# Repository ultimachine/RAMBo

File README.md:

RAMBo 3D Printer electronics
=====

THIS board is based off the Arduino MEGA design and work of RepRap community. It has 5 stepper drivers and 5 mosfet switched outputs.

There is no warantee for these files in any way. They are used to produce these boards, but there may have been some undocumented tweaks by various designers, engineers, manufacturers, suppliers, and assemblers to make this a functional product.

If you have any questions, suggestions, or comments please use the issues tracker at github.org/ultimachine/RAMBo/issues for now.

Please report bugs at github.org/ultimachine/RAMBo/issues

Documentation is at reprap.org/wiki/rambo

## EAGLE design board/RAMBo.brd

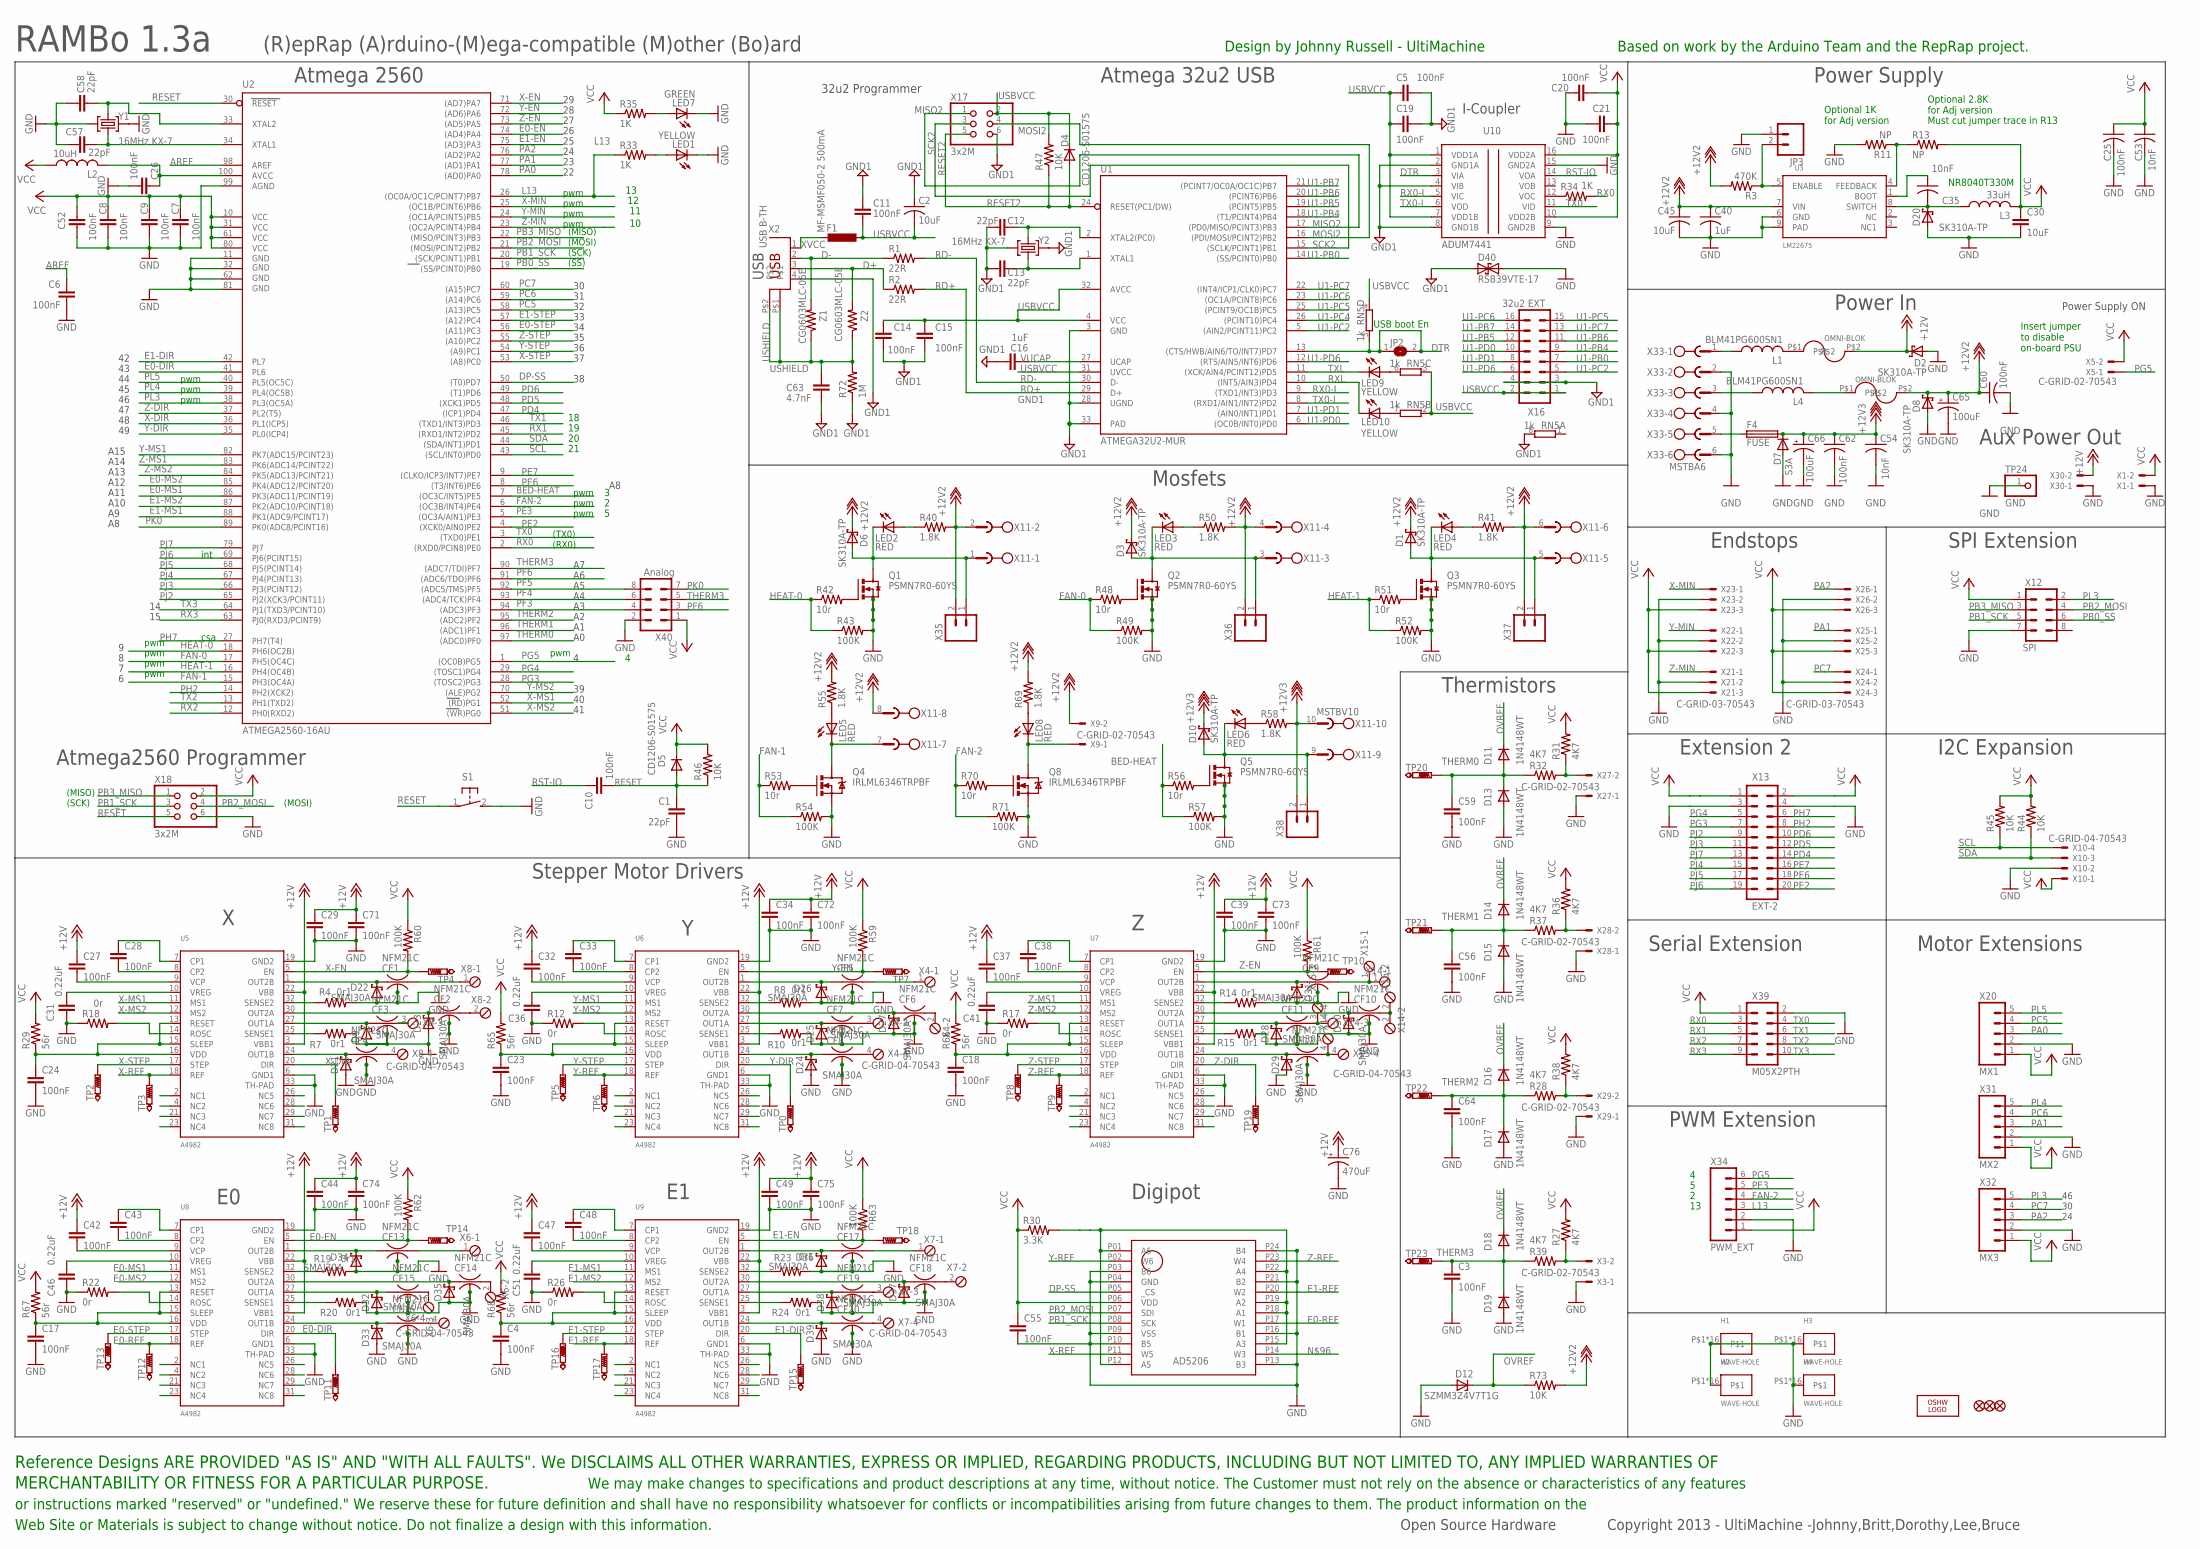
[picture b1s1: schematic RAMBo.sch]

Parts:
C1, C12, C13, C57, C58: 22pF; C0603
C2: 10uF; C0805
C3, C4, C6, C7, C8, C9, C10, C11, C14, C15, C17, C18, C23, C24, C25, C26, C27, C28, C29, C32, C33, C34, C37, C38, C39, C42, C43, C44, C47, C48, C49, C52, C55, C56, C59, C60, C62, C64, C71, C72, C73, C74, C75: 100nF; C0603
C5, C19, C20, C21: 100nF; C0402
C16: 1uF; C0603
C30: 10uF; C1210K
C31, C36, C41, C46, C51: 0.22uF; C0603
C35, C53, C54: 10nF; C0603
C40: 1uF; C0805
C45: 10uF; C2220K
C63: 4.7nF; C0402
C65, C66: 100uF; E3,5-8
C76: 470uF; C12,5-5
CF1, CF2, CF3, CF4, CF5, CF6, CF7, CF8, CF9, CF10, CF11, CF12, CF13, CF14, CF15, CF16, CF17, CF18, CF19, CF20: NFM21C
D1, D2, D3, D6, D8, D10, D20: SK310A-TP; SMA-SM
D4, D5: CD1206-S01575; MINIMELF
D7: S3A; DO-214AB
D9, D21, D22, D23, D24, D25, D26, D27, D28, D29, D30, D31, D32, D33, D34, D35, D36, D37, D38, D39: SMAJ30A; SMA-SM
D11, D13, D14, D15, D16, D17, D18, D19: 1N4148WT; SOD523
D12: SZMM3Z4V7T1G; SOD323-R
D40: RSB39VTE-17; SOD323-R
F1: MF-MSMF050-2 500mA; L1812
F2, F3: OMNI-BLOK
F4: FUSE; FUSE-ATO-SMD
FID1, FID2, FID3: FIDUCIAL1X2.5; FIDUCIAL-1X2.5
H1, H2, H3, H4: WAVE-HOLE; 3,0-WAVE-HOLE
JP2: SJ
JP3: M02PTH; 1X02
L1, L4: BLM41PG600SN1; L1806
L2: 10uH; C0805
L3: 33uH; NR8040
LED1, LED9, LED10: YELLOW; CHIP-LED0805
LED2, LED3, LED4, LED5, LED6, LED8: RED; CHIP-LED0805
LED7: GREEN; CHIP-LED0805
LOGO1: OSHW_LOGO_8MILX0150-NT; OSHW_8X150_NOTEXT
Q1, Q2, Q3, Q5: PSMN7R0-60YS; SOT669
Q4, Q8: IRLML6346TRPBF; SOT23-3
R1, R2: 22R; R0402
R3: 470K; R0603
R4, R7, R8, R10, R14, R15, R19, R20, R23, R24: 0r1; R1206
R11, R13: NP; R0603
R12, R17, R18, R22, R26: 0r; R0603
R27, R28, R31, R32, R36, R37, R38, R39: 4K7; R0603
R29, R65, R66, R67, R68: 56r; R0603
R30: 3.3K; R0603
R33, R34, R35: 1K; R0603
R40, R41, R50, R55, R58, R69: 1.8K; R0603
R42, R48, R51, R53, R56, R70: 10r; R0603
R43, R49, R52, R54, R57, R59, R60, R61, R62, R63, R71: 100K; R0603
R44, R45, R46, R47, R73: 10K; R0603
R72: 1M; R0402
RN5: 1k; CAY16
S1: 31-XX; B3F-31XX
TP0, TP1, TP2, TP3, TP4, TP5, TP6, TP7, TP8, TP9, TP10, TP11, TP12, TP13, TP14, TP15, TP16, TP17, TP18, TP19: PTR1B1,27TH; B1,27TH
TP20, TP21, TP22, TP23: PTR1B1,27; B1,27
TP24: GND; 1X01
U1: ATMEGA32U2-MUR; QFN32TROUND
U2: ATMEGA2560-16AU; TQFP100
U3: LM22675; SOIC127P600X170-9N
U4: AD5206; TSSOP24
U5, U6, U7, U8, U9: A4982; QFN32TROUND
U10: ADUM7441; QSOP16
X1, X3, X5, X9, X27, X28, X29, X30: C-GRID-02-70543; 70543-02
X2: USB B-TH; PN61729
X4, X6, X7, X8, X14, X15: C-GRID-04-70543; 4POL254
X10: C-GRID-04-70543; 70543-04
X11: MSTBV10
X12: SPI; 2X4
X13: EXT-2; 2X10
X16: 32u2 EXT; 2X8
X17, X18: 3x2M; 2X03
X20: MX1; 1X05
X21, X22, X23, X24, X25, X26: C-GRID-03-70543; 70543-03
X31: MX2; 1X05
X32: MX3; 1X05
X33: MSTBA6
X34: PWM_EXT; 1X06
X35, X36, X37, X38: M02PTH; 1X02
X39: M05X2PTH; AVR_ICSP
X40: Analog; 2X4
Y1, Y2: 16MHz KX-7; CRYSTAL-3.2-2.5
Z1, Z2: CG0603MLC-05E; R0603

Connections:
+12V: C27.1, C29.1, C32.1, C34.1, C37.1, C39.1, C42.1, C44.1, C47.1, C49.1, C71.1, C72.1, C73.1, C74.1, C75.1, C76.+, D2.C, F2.P$2, U5.3 (VBB1), U5.22 (VBB), U6.3 (VBB1), U6.22 (VBB), U7.3 (VBB1), U7.22 (VBB), U8.3 (VBB1), U8.22 (VBB), U9.3 (VBB1), U9.22 (VBB), X30.2
+12V2: C40.1, C45.1, C60.1, C65.+, D1.C, D3.C, D6.C, D8.C, F3.P$2, R3.2, R40.2, R41.2, R50.2, R55.2, R69.2, R73.2, U3.7 (VIN), X9.2, X11.2, X11.4, X11.6, X11.8, X35.2, X36.2, X37.2
+12V3: C54.1, C62.1, C66.+, D7.C, D10.C, F4.P$2 (2), R58.2, X11.10, X38.2
AREF: C6.1, U2.98 (AREF)
BED-HEAT: R56.1, R57.1, U2.7 ((OC3C/INT5)PE5)
D+: R2.1, X2.3, Z2.2
D-: R1.1, X2.2, Z1.2
DP-SS: U2.50 ((T0)PD7), U4.P05 (_CS)
DTR: JP2.1, JP2.2, RN5.5 (2), U1.13 ((CTS/HWB/AIN6/TO/INT7)PD7), U10.3 (VIA)
E0-DIR: TP11.TP, U2.41 (PL6), U8.20 (DIR)
E0-EN: R62.2, TP14.TP, U2.74 ((AD4)PA4), U8.5 (EN)
E0-MS1: U2.86 (PK3(ADC11/PCINT19)), U8.11 (MS1)
E0-MS2: U2.85 (PK4(ADC12/PCINT20)), U8.12 (MS2)
E0-REF: TP12.TP, U4.P17 (W1), U8.18 (REF)
E0-STEP: TP13.TP, U2.56 ((A11)PC3), U8.17 (STEP)
E1-DIR: TP15.TP, U2.42 (PL7), U9.20 (DIR)
E1-EN: R63.2, TP18.TP, U2.75 ((AD3)PA3), U9.5 (EN)
E1-MS1: U2.88 (PK1(ADC9/PCINT17)), U9.11 (MS1)
E1-MS2: U2.87 (PK2(ADC10/PCINT18)), U9.12 (MS2)
E1-REF: TP17.TP, U4.P20 (W2), U9.18 (REF)
E1-STEP: TP16.TP, U2.57 ((A12)PC4), U9.17 (STEP)
FAN-0: R48.1, R49.1, U2.17 (PH5(OC4C))
FAN-1: R53.1, R54.1, U2.15 (PH3(OC4A))
FAN-2: R70.1, R71.1, U2.6 ((OC3B/INT4)PE4), X34.4
GND: C1.2, C3.2, C4.2, C6.2, C7.2, C8.2, C9.2, C17.2, C18.2, C20.2, C21.1, C23.2, C24.2, C25.2, C26.2, C29.2, C30.2, C31.1, C34.2, C36.1, C39.2, C40.2, C41.1, C44.2, C45.2, C46.1, C49.2, C51.1, C52.2, C53.2, C54.2, C55.2, C56.2, C57.2, C58.2, C59.2, C60.2, C62.2, C64.2, C65.-, C66.-, C71.2, C72.2, C73.2, C74.2, C75.2, C76.-, CF1.2@1 (2), CF1.2@2 (2), CF2.2@1 (2), CF2.2@2 (2), CF3.2@1 (2), CF3.2@2 (2), CF4.2@1 (2), CF4.2@2 (2), CF5.2@1 (2), CF5.2@2 (2), CF6.2@1 (2), CF6.2@2 (2), CF7.2@1 (2), CF7.2@2 (2), CF8.2@1 (2), CF8.2@2 (2), CF9.2@1 (2), CF9.2@2 (2), CF10.2@1 (2), CF10.2@2 (2), CF11.2@1 (2), CF11.2@2 (2), CF12.2@1 (2), CF12.2@2 (2), CF13.2@1 (2), CF13.2@2 (2), CF14.2@1 (2), CF14.2@2 (2), CF15.2@1 (2), CF15.2@2 (2), CF16.2@1 (2), CF16.2@2 (2), CF17.2@1 (2), CF17.2@2 (2), CF18.2@1 (2), CF18.2@2 (2), CF19.2@1 (2), CF19.2@2 (2), CF20.2@1 (2), CF20.2@2 (2), D2.A, D7.A, D8.A, D9.A, D12.A, D13.A, D15.A, D17.A, D19.A, D20.A, D21.A, D22.A, D23.A, D24.A, D25.A, D26.A, D27.A, D28.A, D29.A, D30.A, D31.A, D32.A, D33.A, D34.A, D35.A, D36.A, D37.A, D38.A, D39.A, D40.C (2), H1.P$1, H1.P$2, H1.P$3, H1.P$4, H1.P$5, H1.P$6, H1.P$7, H1.P$8, H1.P$17, H1.P$18, H1.P$19, H1.P$20, H1.P$21, H1.P$22, H1.P$23, H1.P$24, H2.P$1, H2.P$2, H2.P$3, H2.P$4, H2.P$5, H2.P$6, H2.P$7, H2.P$8, H2.P$17, H2.P$18, H2.P$19, H2.P$20, H2.P$21, H2.P$22, H2.P$23, H2.P$24, H3.P$1, H3.P$2, H3.P$3, H3.P$4, H3.P$5, H3.P$6, H3.P$7, H3.P$8, H3.P$17, H3.P$18, H3.P$19, H3.P$20, H3.P$21, H3.P$22, H3.P$23, H3.P$24, H4.P$1, H4.P$2, H4.P$3, H4.P$4, H4.P$5, H4.P$6, H4.P$7, H4.P$8, H4.P$17, H4.P$18, H4.P$19, H4.P$20, H4.P$21, H4.P$22, H4.P$23, H4.P$24, JP3.1, LED1.C, LED7.C, Q1.1 (S), Q1.2 (S), Q1.3 (S), Q2.1 (S), Q2.2 (S), Q2.3 (S), Q3.1 (S), Q3.2 (S), Q3.3 (S), Q4.2 (S), Q5.1 (S), Q5.2 (S), Q5.3 (S), Q8.2 (S), R4.2, R7.2, R8.2, R10.2, R11.2, R12.1, R14.2, R15.2, R17.1, R18.1, R19.2, R20.2, R22.1, R23.2, R24.2, R26.1, R43.2, R49.2, R52.2, R54.2, R57.2, R71.2, S1.2 (S), TP24.1, U2.11 (GND), U2.32 (GND1), U2.62 (GND2), U2.81 (GND3), U2.99 (AGND), U3.6 (GND), U3.9 (PAD), U4.P03 (B6), U4.P04 (GND), U4.P09 (VSS), U4.P10 (B5), U4.P13 (B3), U4.P16 (B1), U4.P21 (B2), U4.P24 (B4), U5.6 (GND1), U5.19 (GND2), U5.33 (TH-PAD), U6.6 (GND1), U6.19 (GND2), U6.33 (TH-PAD), U7.6 (GND1), U7.19 (GND2), U7.33 (TH-PAD), U8.6 (GND1), U8.19 (GND2), U8.33 (TH-PAD), U9.6 (GND1), U9.19 (GND2), U9.33 (TH-PAD), U10.9 (GND2B), U10.15 (GND2A), X1.1, X3.1, X10.2, X12.7, X13.3, X13.4, X18.6, X20.2, X21.2, X22.2, X23.2, X24.2, X25.2, X26.2, X27.1, X28.1, X29.1, X30.1, X31.2, X32.2, X33.2, X33.4, X33.6, X34.2, X39.2, X40.2, Y1.2 (GND), Y1.4 (GND)
GND1: C2.1, C5.2, C11.2, C12.2, C13.2, C14.2, C15.2, C16.2, C19.2, C63.2, D40.A (1), R72.1, RN5.8 (2), U1.3 (GND), U1.28 (UGND), U1.33 (PAD), U10.2 (GND1A), U10.4 (VIB), U10.8 (GND1B), X2.4, X16.3, X16.4, X17.6, Y2.2 (GND), Y2.4 (GND)
HEAT-0: R42.1, R43.1, U2.18 (PH6(OC2B))
HEAT-1: R51.1, R52.1, U2.16 (PH4(OC4B))
L13: R33.1, U2.26 ((OC0A/OC1C/PCINT7)PB7), X34.3
MISO2: U1.17 ((PD0/MISO/PCINT3)PB3), X17.1
MOSI2: U1.16 ((PDI/MOSI/PCINT2)PB2), X17.4
unnamed: C31.2, U5.10 (VREG)
unnamed: LED1.A, R33.2
unnamed: LED7.A, R35.2
unnamed: R8.1, U6.32 (SENSE2)
unnamed: R10.1, U6.25 (SENSE1)
unnamed: C33.2, U6.8 (CP2)
unnamed: C32.2, U6.9 (VCP)
unnamed: C36.2, U6.10 (VREG)
unnamed: R12.2, U6.14 (ROSC)
unnamed: Q4.1 (G), R53.2
unnamed: LED10.A, RN5.7 (2)
unnamed: C24.1, R29.1, U5.13 (RESET), U5.15 (SLEEP), U5.16 (VDD)
unnamed: L1.P$1 (1), X33.1
unnamed: F3.P$1, L4.P$2 (2)
unnamed: JP3.2, R3.1, U3.5 (ENABLE)
unnamed: F4.P$1 (1), X33.5
unnamed: CF5.1, D26.C, U6.1 (OUT2B)
unnamed: CF20.3, X7.4
unnamed: CF5.3, X4.1
unnamed: CF6.1, D27.C, U6.30 (OUT2A)
unnamed: D6.A, LED2.C, Q1.MB (D), X11.1, X35.1
unnamed: R4.1, U5.32 (SENSE2)
unnamed: CF7.1, D25.C, U6.27 (OUT1A)
unnamed: C33.1, U6.7 (CP1)
unnamed: C23.1, R65.1, U6.13 (RESET), U6.15 (SLEEP), U6.16 (VDD)
unnamed: Q2.4 (G), R48.2
unnamed: C26.1, L2.2, U2.100 (AVCC)
unnamed: R14.1, U7.32 (SENSE2)
unnamed: R15.1, U7.25 (SENSE1)
unnamed: C38.2, U7.8 (CP2)
unnamed: C37.2, U7.9 (VCP)
unnamed: C41.2, U7.10 (VREG)
unnamed: R17.2, U7.14 (ROSC)
unnamed: CF10.1, D30.C, U7.30 (OUT2A)
unnamed: CF11.1, D28.C, U7.27 (OUT1A)
unnamed: R7.1, U5.25 (SENSE1)
unnamed: C28.2, U5.8 (CP2)
unnamed: C27.2, U5.9 (VCP)
unnamed: CF19.3, X7.3
unnamed: CF12.1, D29.C, U7.24 (OUT1B)
unnamed: CF12.3, X14.4, X15.4
unnamed: C38.1, U7.7 (CP1)
unnamed: R18.2, U5.14 (ROSC)
unnamed: C18.1, R66.1, U7.13 (RESET), U7.15 (SLEEP), U7.16 (VDD)
unnamed: LED8.C, Q8.3 (D), X9.1
unnamed: R19.1, U8.32 (SENSE2)
unnamed: CF1.1, D22.C, U5.1 (OUT2B)
unnamed: C28.1, U5.7 (CP1)
unnamed: R20.1, U8.25 (SENSE1)
unnamed: C43.2, U8.8 (CP2)
unnamed: CF3.1, D9.C, U5.27 (OUT1A)
unnamed: CF4.1, D21.C, U5.24 (OUT1B)
unnamed: LED9.A, RN5.6 (2)
unnamed: R34.1, U10.12 (VOC)
unnamed: C42.2, U8.9 (VCP)
unnamed: C46.2, U8.10 (VREG)
unnamed: R22.2, U8.14 (ROSC)
unnamed: CF13.1, D34.C, U8.1 (OUT2B)
unnamed: CF13.3, X6.1
unnamed: CF14.1, D35.C, U8.30 (OUT2A)
unnamed: CF15.1, D32.C, U8.27 (OUT1A)
unnamed: C43.1, U8.7 (CP1)
unnamed: C17.1, R67.1, U8.13 (RESET), U8.15 (SLEEP), U8.16 (VDD)
unnamed: CF18.3, X7.2
unnamed: R23.1, U9.32 (SENSE2)
unnamed: R24.1, U9.25 (SENSE1)
unnamed: C48.2, U9.8 (CP2)
unnamed: C47.2, U9.9 (VCP)
unnamed: C51.2, U9.10 (VREG)
unnamed: R26.2, U9.14 (ROSC)
unnamed: CF20.1, D39.C, U9.24 (OUT1B)
unnamed: CF19.1, D38.C, U9.27 (OUT1A)
unnamed: CF17.1, D36.C, U9.1 (OUT2B)
unnamed: CF18.1, D37.C, U9.30 (OUT2A)
unnamed: C48.1, U9.7 (CP1)
unnamed: C4.1, R68.1, U9.13 (RESET), U9.15 (SLEEP), U9.16 (VDD)
unnamed: LED8.A, R69.1
unnamed: Q8.1 (G), R70.2
unnamed: LED2.A, R40.1
unnamed: R30.2, U4.P01 (A6), U4.P12 (A5), U4.P15 (A3), U4.P18 (A1), U4.P19 (A2), U4.P22 (A4)
unnamed: R31.1, R32.2, X27.2
unnamed: Q1.4 (G), R42.2
unnamed: R36.1, R37.2, X28.2
unnamed: Q3.4 (G), R51.2
unnamed: R28.2, R38.1, X29.2
unnamed: Q5.4 (G), R56.2
unnamed: CF17.3, X7.1
unnamed: CF16.3, X6.4
unnamed: CF15.3, X6.3
unnamed: D3.A, LED3.C, Q2.MB (D), X11.3, X36.1
unnamed: LED3.A, R50.1
unnamed: D1.A, LED4.C, Q3.MB (D), X11.5, X37.1
unnamed: LED4.A, R41.1
unnamed: LED5.C, Q4.3 (D), X11.7
unnamed: LED5.A, R55.1
unnamed: D10.A, LED6.C, Q5.MB (D), X11.9, X38.1
unnamed: LED6.A, R58.1
unnamed: CF14.3, X6.2
unnamed: CF16.1, D33.C, U8.24 (OUT1B)
unnamed: CF4.3, X8.4
unnamed: CF3.3, X8.3
unnamed: R27.1, R39.2, X3.2
unnamed: CF2.3, X8.2
unnamed: C35.1, U3.1 (BOOT)
unnamed: CF1.3, X8.1
unnamed: CF8.3, X4.4
unnamed: CF7.3, X4.3
unnamed: R11.1, R13.1, U3.4 (FEEDBACK)
unnamed: C35.2, D20.C, L3.P$1 (1), U3.8 (SWITCH)
unnamed: CF6.3, X4.2
unnamed: CF8.1, D24.C, U6.24 (OUT1B)
unnamed: CF9.1, D31.C, U7.1 (OUT2B)
unnamed: CF11.3, X14.3, X15.3
unnamed: CF9.3, X14.1, X15.1
unnamed: CF10.3, X14.2, X15.2
unnamed: F2.P$1, L1.P$2 (2)
unnamed: CF2.1, D23.C, U5.30 (OUT2A)
unnamed: L4.P$1 (1), X33.3
OVREF: D11.C, D12.C, D14.C, D16.C, D18.C, R73.1
PA0: U2.78 ((AD0)PA0), X20.3
PA1: U2.77 ((AD1)PA1), X25.1, X31.3
PA2: U2.76 ((AD2)PA2), X26.1, X32.3
PB0_SS: U2.19 ((SS/PCINT0)PB0), X12.6
PB1_SCK: U2.20 ((SCK/PCINT1)PB1), U4.P08 (SCK), X12.5, X18.3
PB2_MOSI: U2.21 ((MOSI/PCINT2)PB2), U4.P07 (SDI), X12.4, X18.4
PB3_MISO: U2.22 ((MISO/PCINT3)PB3), X12.3, X18.1
PC5: U2.58 ((A13)PC5), X20.4
PC6: U2.59 ((A14)PC6), X31.4
PC7: U2.60 ((A15)PC7), X24.1, X32.4
PD4: U2.47 ((ICP1)PD4), X13.14
PD5: U2.48 ((XCK1)PD5), X13.12
PD6: U2.49 ((T1)PD6), X13.10
PE2: U2.4 ((XCK0/AIN0)PE2), X13.20
PE3: U2.5 ((OC3A/AIN1)PE3), X34.5
PE6: U2.8 ((T3/INT6)PE6), X13.18
PE7: U2.9 ((CLKO/ICP3/INT7)PE7), X13.16
PF3: U2.94 ((ADC3)PF3), X40.4
PF4: U2.93 ((ADC4/TCK)PF4), X40.6
PF5: U2.92 ((ADC5/TMS)PF5), X40.8
PF6: U2.91 ((ADC6/TDO)PF6), X40.3
PG3: U2.28 ((TOSC2)PG3), X13.7
PG4: U2.29 ((TOSC1)PG4), X13.5
PG5: U2.1 ((OC0B)PG5), X5.1, X34.6
PH2: U2.14 (PH2(XCK2)), X13.8
PH7: U2.27 (PH7(T4)), X13.6
PJ2: U2.65 (PJ2(XCK3/PCINT11)), X13.9
PJ3: U2.66 (PJ3(PCINT12)), X13.11
PJ4: U2.67 (PJ4(PCINT13)), X13.15
PJ5: U2.68 (PJ5(PCINT14)), X13.17
PJ6: U2.69 (PJ6(PCINT15)), X13.19
PJ7: U2.79 (PJ7), X13.13
PK0: U2.89 (PK0(ADC8/PCINT16)), X40.7
PL3: U2.38 (PL3(OC5A)), X12.2, X32.5
PL4: U2.39 (PL4(OC5B)), X31.5
PL5: U2.40 (PL5(OC5C)), X20.5
RD+: R2.2, U1.29 (D+)
RD-: R1.2, U1.30 (D-)
RESET: C1.1, C10.2, D5.A, R46.1, S1.1, U2.30 (RESET), X18.5
RESET2: D4.A, R47.1, U1.24 (RESET(PC1/DW)), X17.5
RST-IO: C10.1, U10.14 (VOA)
RX0: R34.2, U2.2 ((RXD0/PCIN8)PE0), X39.3
RX0-I: U1.9 ((TXD1/INT3)PD3), U10.5 (VIC)
RX1: U2.45 ((RXD1/INT2)PD2), X39.5
RX2: U2.12 (PH0(RXD2)), X39.7
RX3: U2.63 (PJ0(RXD3/PCINT9)), X39.9
RXL: LED10.C, U1.10 ((INT5/AIN3)PD4)
SCK2: U1.15 ((SCLK/PCINT1)PB1), X17.3
SCL: R45.1, U2.43 ((SCL/INT0)PD0), X10.4
SDA: R44.1, U2.44 ((SDA/INT1)PD1), X10.3
THERM0: C59.1, D11.A, D13.C, R32.1, TP20.TP, U2.97 ((ADC0)PF0)
THERM1: C56.1, D14.A, D15.C, R37.1, TP21.TP, U2.96 ((ADC1)PF1)
THERM2: C64.1, D16.A, D17.C, R28.1, TP22.TP, U2.95 ((ADC2)PF2)
THERM3: C3.1, D18.A, D19.C, R39.1, TP23.TP, U2.90 ((ADC7/TDI)PF7), X40.5
TX0: U2.3 ((TXD0)PE1), U10.11 (VID), X39.4
TX0-I: U1.8 ((RXD1/AIN1/INT2)PD2), U10.6 (VOD)
TX1: U2.46 ((TXD1/INT3)PD3), X39.6
TX2: U2.13 (PH1(TXD2)), X39.8
TX3: U2.64 (PJ1(TXD3/PCINT10)), X39.10
TXL: LED9.C, U1.11 ((XCK/AIN4/PCINT12)PD5)
U1-PB0: U1.14 ((SS/PCINT0)PB0), X16.7
U1-PB4: U1.18 ((T1/PCINT4)PB4), X16.9
U1-PB5: U1.19 ((PCINT5)PB5), X16.12
U1-PB6: U1.20 ((PCINT6)PB6), X16.11
U1-PB7: U1.21 ((PCINT7/OC0A/OC1C)PB7), X16.14
U1-PC2: U1.5 ((AIN2/PCINT11)PC2), X16.5
U1-PC4: U1.26 ((PCINT10)PC4)
U1-PC5: U1.25 ((PCINT9/OC1B)PC5), X16.15
U1-PC6: U1.23 ((OC1A/PCINT8)PC6), X16.16
U1-PC7: U1.22 ((INT4/ICP1/CLK0)PC7), X16.13
U1-PD0: U1.6 ((OC0B/INT0)PD0), X16.10
U1-PD1: U1.7 ((AIN0/INT1)PD1), X16.8
U1-PD6: U1.12 ((RTS/AIN5/INT6)PD6), X16.6
USBVCC: C2.2, C5.1, C11.1, C14.1, C15.1, C19.1, D4.C, F1.1, R47.2, RN5.2 (1), RN5.3 (1), RN5.4 (1), U1.4 (VCC), U1.31 (UVCC), U1.32 (AVCC), U10.1 (VDD1A), U10.7 (VDD1B), X16.1, X16.2, X17.2
USHIELD: C63.1, R72.2, X2.P$1, X2.P$2, Z1.1, Z2.1
VCC: C7.1, C8.1, C9.1, C20.1, C21.2, C25.1, C30.1, C52.1, C53.1, C55.1, D5.C, L2.1, L3.P$2 (2), R13.2, R27.2, R29.2, R30.1, R31.2, R35.1, R36.2, R38.2, R44.2, R45.2, R46.2, R59.1, R60.1, R61.1, R62.1, R63.1, R65.2, R66.2, R67.2, R68.2, U2.10 (VCC), U2.31 (VCC1), U2.61 (VCC2), U2.80 (VCC3), U4.P06 (VDD), U10.10 (VDD2B), U10.16 (VDD2A), X1.2, X5.2, X10.1, X12.1, X13.1, X13.2, X18.2, X20.1, X21.3, X22.3, X23.3, X24.3, X25.3, X26.3, X31.1, X32.1, X34.1, X39.1, X40.1
VUCAP: C16.1, U1.27 (UCAP)
X-DIR: TP1.TP, U2.36 (PL1(ICP5)), U5.20 (DIR)
X-EN: R60.2, TP4.TP, U2.71 ((AD7)PA7), U5.5 (EN)
X-MIN: U2.25 ((OC1B/PCINT6)PB6), X23.1
X-MS1: U2.52 ((RD)PG1), U5.11 (MS1)
X-MS2: U2.51 ((WR)PG0), U5.12 (MS2)
X-REF: TP3.TP, U4.P11 (W5), U5.18 (REF)
X-STEP: TP2.TP, U2.53 ((A8)PC0), U5.17 (STEP)
XT1: C13.1, U1.1 (XTAL1), Y2.1 (C1)
XT2: C12.1, U1.2 (XTAL2(PC0)), Y2.3 (C2)
XTAL1: C57.1, U2.34 (XTAL1), Y1.1 (C1)
XTAL2: C58.1, U2.33 (XTAL2), Y1.3 (C2)
XVCC: F1.2, X2.1
Y-DIR: TP0.TP, U2.35 (PL0(ICP4)), U6.20 (DIR)
Y-EN: R59.2, TP7.TP, U2.72 ((AD6)PA6), U6.5 (EN)
Y-MIN: U2.24 ((OC1A/PCINT5)PB5), X22.1
Y-MS1: U2.82 (PK7(ADC15/PCINT23)), U6.11 (MS1)
Y-MS2: U2.70 ((ALE)PG2), U6.12 (MS2)
Y-REF: TP6.TP, U4.P02 (W6), U6.18 (REF)
Y-STEP: TP5.TP, U2.54 ((A9)PC1), U6.17 (STEP)
Z-DIR: TP19.TP, U2.37 (PL2(T5)), U7.20 (DIR)
Z-EN: R61.2, TP10.TP, U2.73 ((AD5)PA5), U7.5 (EN)
Z-MIN: U2.23 ((OC2A/PCINT4)PB4), X21.1
Z-MS1: U2.83 (PK6(ADC14/PCINT22)), U7.11 (MS1)
Z-MS2: U2.84 (PK5(ADC13/PCINT21)), U7.12 (MS2)
Z-REF: TP9.TP, U4.P23 (W4), U7.18 (REF)
Z-STEP: TP8.TP, U2.55 ((A10)PC2), U7.17 (STEP)

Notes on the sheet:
(SCK)
(MISO)
(MOSI)
pwm
(TX0)
(RX0)
USB boot En
int
csa
(SS)
Reference Designs ARE PROVIDED "AS IS" AND "WITH ALL FAULTS". We DISCLAIMS ALL OTHER WARRANTIES, EXPRESS OR IMPLIED, REGARDING PRODUCTS, INCLUDING BUT NOT LIMITED TO, ANY IMPLIED WARRANTIES OF
MERCHANTABILITY OR FITNESS FOR A PARTICULAR PURPOSE.
or instructions marked "reserved" or "undefined." We reserve these for future definition and shall have no responsibility whatsoever for conflicts or incompatibilities arising from future changes to them. The product information on the
Web Site or Materials is subject to change without notice. Do not finalize a design with this information.
A10
A11
A12
A13
A14
A15
Motor Extensions
SPI Extension
PWM Extension
RAMBo 1.3a
Atmega 32u2 USB
I2C Expansion
Atmega2560 Programmer
Power In
Power Supply
Stepper Motor Drivers
Digipot
Thermistors
Mosfets
Aux Power Out
Design by Johnny Russell - UltiMachine
Based on work by the Arduino Team and the RepRap project.
(R)epRap (A)rduino-(M)ega-compatible (M)other (Bo)ard
Serial Extension
Endstops
Atmega 2560

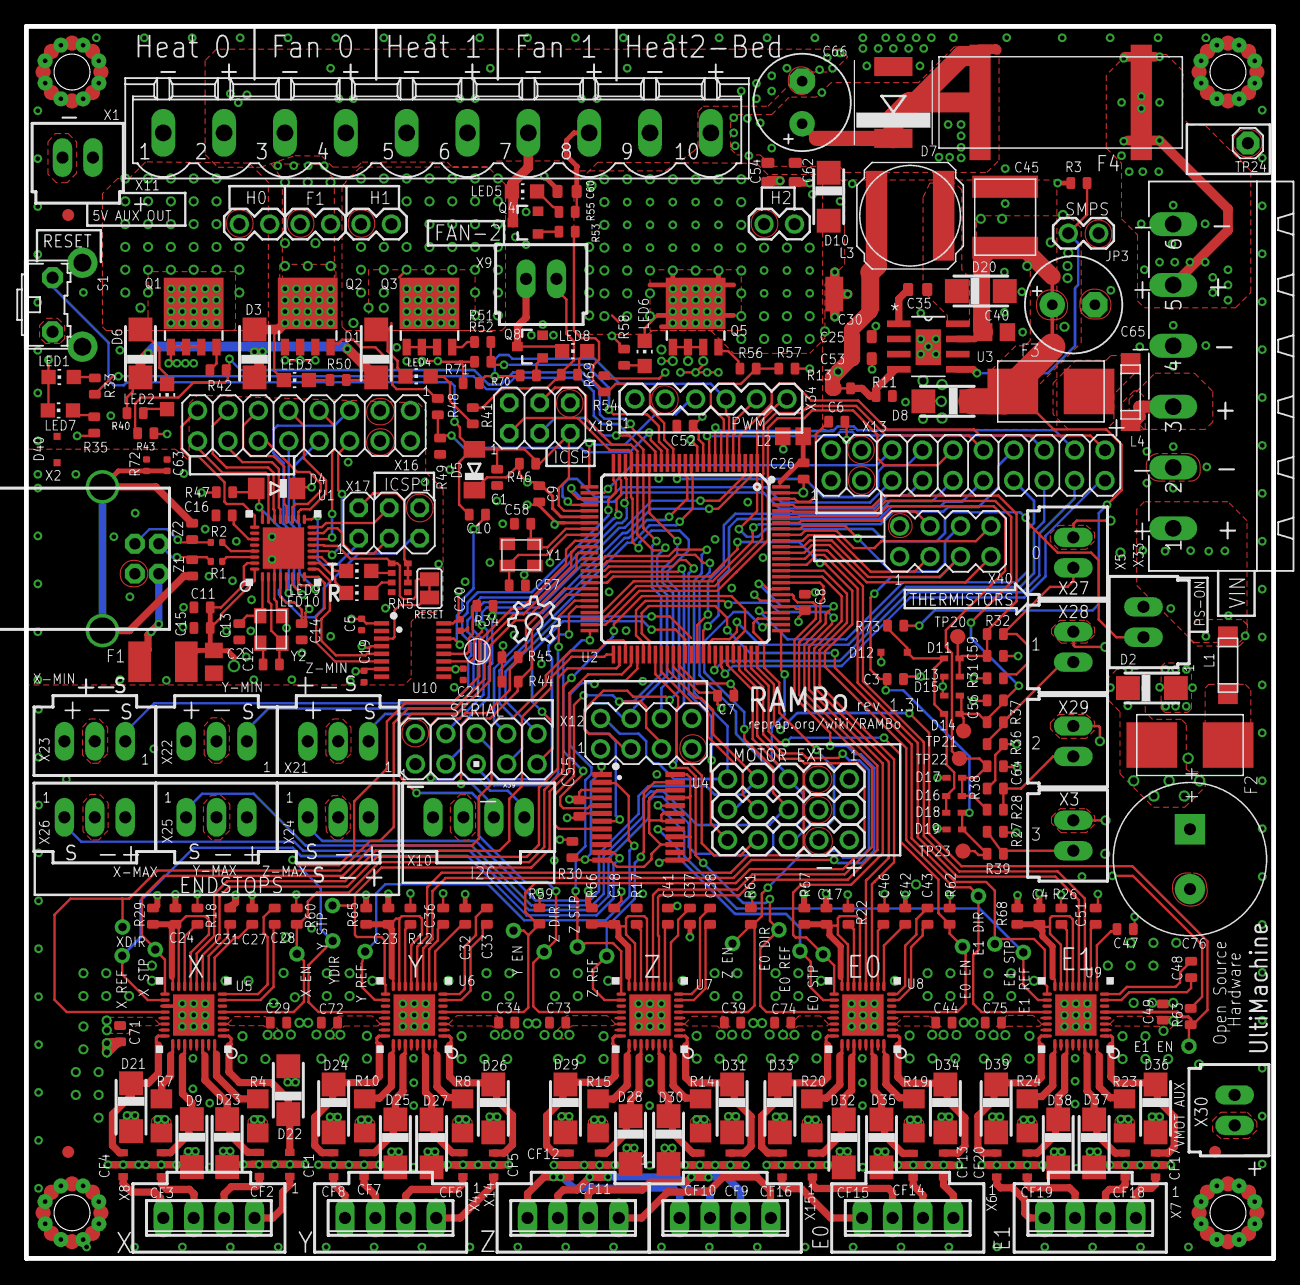
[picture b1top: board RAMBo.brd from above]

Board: 4 copper layers, 104.1 x 102.9 mm, 309 parts (0 on the bottom side), 252 nets.

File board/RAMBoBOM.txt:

Qty;Value;Device;Package;Description;Manufacturer;MPN;Parts
1;;31-XX;B3F-31XX;SWITCH, TACTILE, SPST-NO, 50mA, THD ;Omron;1571610-2;S1
1;;M02PTH;1X02;1x2 header;;2211S-02G;JP3, X35, X36, X37, X38
5;0.22uF;C-EUC0603;C0603;0.22uF 100V capacitor X or 15%;Yageo;CC0603KRX7R7BB224 ;C31, C36, C41, C46, C51
5;0r;R-US_R0603;R0603;0r (zero ohm) 100mW 5% resistor;Bourns;CR0603-J/-000ELF ;R12, R17, R18, R22, R26
10;0r1;R-US_R1206;R1206;0r1 (0.1ohm) .5mW 1% resistor;Bourns;CRM1206-FX-R100ELF ;R4, R7, R8, R10, R14, R15, R19, R20, R23, R24
6;1.8K;R-US_R0603;R0603;;;RC0603JR-071K8L;R40, R41, R50, R55, R58, R69
11;100K;R-US_R0603;R0603;100Kohm 100mW 1% resistor;Yageo;RC0603FR-07100KL;R43, R49, R52, R54, R57, R59, R60, R61, R62, R63, R71
45;100nF;C-EU0603-RND;C0603-ROUND;0.1uF 50V capacitor;Kemet;C0603C104K5RACTU ;C6, C7, C8, C9, C10, C11, C14, C15, C26, C52, C67, C68, C3, C4, C17, C18, C23, C24, C27, C28, C29, C32, C33, C34, C37, C38, C39, C42, C43, C44, C47, C48, C49, C55, C56, C59, C64, C71, C72, C73, C74, C75, C25, C60, C62
2;100uF;CPOL-USE3.5-8;E3,5-8;Aluminum Electrolytic Capacitors - Leaded 100uF 50V 20% 105c ;Nichicon;UVZ1H101MPD1TD;C65, C66
5;10K;R-US_R0603;R0603;10Kohm 100mW 1% resistor;Panasonic;ERJ3EKF1002V ;R44, R45, R46, R47, R73
5;10nF;C-USC0603;C0603;10nF (0.01uF) 25V capacitor;TDK;C1608X7R1E103K ;C35, C53, C54, C69, C70
6;10r;R-US_R0603;R0603;10r (10ohm) 100mW 1% resistor;Vishay;CRCW060310R0FKEA;R42, R48, R51, R53, R56, R70
1;10uF;C-EUC1210K;C1210K;Multilayer Ceramic Capacitors MLCC - SMD/SMT 1210 10uF 25volts X5R 10% ;TDK;C3225X5R1E106K;C30
1;10uF;C-USC0805;C0805;10uF;Kemet;C0805C106K8PACTU;C2
1;10uF;C-USC2220K;C2220K;10uF;TDK;C5750X7R1H106M;C45
2;16MHz KX-7;CRYSTAL-3.2-2.5;CRYSTAL-3.2-2.5;16MHz KX-7 10ppm crystal;TXC;7m-16.000MEEQ-T;Y1, Y2
3;1K;R-US_R0603;R0603;RESISTOR, THICK FILM, 1KOHM, 100mW, 1% ;Panasonic;ERJ3EKF1001V ;R33, R34, R35
1;1M;R-US_R0402;R0402;RES 1M OHM 1/10W 5% 0402 SMD;Panasonic;ERJ-2GEJ105X;R72
8;1N4148WT;1N4148WT;SOD523;iode Small Signal Switching 75V 2-Pin SOD-523F T/R ;Fairchild;1N4148WT ;D11, D13, D14, D15, D16, D17, D18, D19
1;1k;4R-NCAY16;CAY16;Resistor Networks & Arrays 1K 5% Convex 4resistors ;Bourns;CAY16-102J4LF;RN5
1;1uF;C-EU0603-RND;C0603-ROUND;1uF 10V capacitor;yageo;CC0603ZRY5V6BB105 ;C16
1;1uF;C-USC0805;C0805;Multilayer Ceramic Capacitors MLCC - SMD/SMT 1.0UF 50V 10% 0805  ;Murata;GRM21BR71H105KA12L ;C40
2;22R;R-US_R0402;R0402;22R (22ohm) 62.5mW 1% resistor;Yageo;RC0402FR-0722RL;R1, R2
5;22pF;C-EU0603-RND;C0603-ROUND;22pF 50V capacitor;TDK;C1608C0G1H220J;C1, C12, C13, C57, C58
1;3.3K;R-US_R0603;R0603;RESISTOR, THICK FILM, 3.3KOHM, 100mW, 5% ;panasonic;erj3geyj332v;R30
0;32u2 EXT;M08X2;2X8;2x8 header;;;X16
1;33uH;L-USNR8040;NR8040;Fixed Inductors 33uH ;TDK;VLP8040T-330M;L3
2;3x2M;PINHD-2X3;2X03;2x3 header;;2213S-06G;X17, X18
1;4.7nF;C-EUC0402;C0402;;;CC0402KRX7R8BB472;C63
1;470K;R-US_R0603;R0603;;;CRCW0603470KFKEA ;R3
1;470uF;CPOL-USC12,5-5;C12,5-5;CAPACITOR ALUM ELEC, 470UF, 50V, 20%, RADIAL;nichicon;UPW1H471MHD1TO;C76
8;4K7;R-US_R0603;R0603;4K7 (4.7Kohm) 100mW 1% resistor;Panasonic;ERJ3EKF4701V ;R27, R28, R31, R32, R36, R37, R38, R39
5;56r;R-US_R0603;R0603;RESISTOR, THICK FILM, 56OHM, 100mW, 5% ;Vishay;CRCW060356R0JNEA ;R29, R65, R66, R67, R68
5;A4982;A4982QFN32ROUNDPADS;QFN32TROUND;A4982;Allegro;A4982SETTR-T;U5, U6, U7, U8, U9
1;AD5206;AD5206;TSSOP24;AD5206 (IC);;AD5206BRUZ10;U4
1;ADUM7441;ADUM7441;QSOP16;;;ADUM7441ARQZ-RL7;U10
1;ATMEGA2560-16AU;ATMEGA25602560-16AU;TQFP100;ATMEGA2560-16AU (IC);;ATMEGA2560-16AU;U2
1;ATMEGA32U2-MUR;ATMEGA16U2-MU;MLF32;ATMEGA32U2-MUR (IC);Atmega;ATMEGA32U2-MU;U1
0;B240A-13-F;SCHOTTKY-DIODE;SMA-SM;40V 2A Diode;Diodes Inc.;B240A-13-F;D1, D3, D6, D10
6;C-GRID-02-70543;C-GRID-02-70543;70543-02;WIRE-BOARD CONNECTOR HEADER 2POS, 2.54MM ;Molex;70543-0001 ;X1, X3, X5, X9, X27, X28, X29, X30
6;C-GRID-03-70543;C-GRID-03-70543;70543-03;WIRE-BOARD CONNECTOR HEADER 3POS, 2.54MM ;Molex;70543-0002 ;X21, X22, X23, X24, X25, X26
7;C-GRID-04-70543;MPT4;4POL254;WIRE-BOARD CONNECTOR HEADER 4POS, 2.54MM ;Molex;70543-0038 ;X4, X6, X7, X8, X10, X14, X15
1;10uH;L-US;C0805;INDUCTOR 10UH 20% 0805 SMD;Taiyo Yuden;CBC2012T100M;L2
2;CD1206-S01575;DIODE-MINIMELF;MINIMELF;100V 150mA diode;Bourns;CD1206-S01575;D4, D5
2;CG0603MLC-05E;VARISTORCN0603;CT/CN0603;5V 20V varistor;Bourns;CG0603MLC-05E;Z1, Z2
1;EXT-2;M10X2;2X10;2x10 header;;2213S-20G ;X13
1;FUSE;FUSE;FUSE-ATO-SMD;FUSE HOLDER, AUTO BLADE, SMT ;Keystone;3587TR ;F4
1;GREEN;LEDCHIP-LED0805;CHIP-LED0805;GREEN LED;;5988170107F ;LED7
2;IRLML6346TRPBF;MOSFET-NCHANNELSMD;SOT23-3;N CH MOSFET, 30V, 3.4A, 3-SOT-23;;IRLML6346TRPBF;Q4, Q8
1;LM22675;LM22675;SOIC127P600X170-9N;;;LM22675MRE-5.0/NOPB;U3
1;M05PTH;M05PTH;1X05;1x5;;2211S-05G;X20
2;M05X2PTH;M05X2PTH;AVR_ICSP;2x5 header;;2213S-10G;X39, X32
1;MF-MSMF050-2 500mA;L-EUL1812;L1812;500mA 15V fuse ptc reset;Bourns;MF-MSMF050-2;F1
1;MSTBA6;MSTBA6;MSTBA6;6 pin fixed terminal block;Molex;39532-1006;X33
1;MSTBV10;MSTBV10;MSTBV10;CONN HEADER 10POS 5.08MM STR TIN;Molex;39531-1010;X11
2;OMNI-BLOK;OMNI-BLOK;OMNI-BLOK;5A fuse/fuse block;Littlefuse;0154005.DR;F2, F3
4;PSMN7R0-60YS;PH7030L;SOT669;PH7030L (Mosfet) 60V 356A 117W;NXP;PSMN7R0-60YS,115;Q1, Q2, Q3, Q5
1;PWM_EXT;M06SIP;1X06;1x6 header;;2213S-06G;X34
6;RED;LEDCHIP-LED0805;CHIP-LED0805;RED;Dialight;5988110107F ;LED2, LED3, LED4, LED5, LED6, LED8
1;S3A;DIODE-D0-214AB;DO-214AB;3A 50V Diode;;S3A;D7
7;SK310A-TP;SCHOTTKY-DIODE;SMA-SM;DIODE SCHOTTKY 100V 3A SMA ;;SK310A-TP;D2, D8, D20,D1, D3, D6, D10
2;SPI;M04X2;2X4;M04X2;;2213S-08G ;X12, X40
1;SZMM3Z4V7T1G;ZENER-DIODESOD323;SOD323-R;;;SZMM3Z4V7T1G;D12
1;USB B-TH;PN61729;PN61729;USB B-TH connector;FCI;61729-0010BLF;X2
3;YELLOW;LEDCHIP-LED0805;CHIP-LED0805;YELLOW LED;Dialight;    5988140107F;LED1, LED9, LED10
1;;;;;;;Bar Code Label
1;;;;PCB;;RAMBoPCB1.2;PCB
;;;;;;;
0.012;;;;white wire;;;White Wire
0.008;;;;black wire;;;Black Wire
34;;;;CONTACT, FEMALE, 30-24AWG, CRIMP ;molex;55H2477 ;loose gold connectors
0;;;;5A fuse;;0448005.MR;replacement fuses
5;;;;TERMINAL BLOCK, PLUGGABLE, 2 POS, 24-12AWG ;Molex;39530-0002;2pos 5.08mm Pluggable
1;;;;TERMINAL BLOCK PLUGGABLE, 6POS, 24-12AWG ;Molex;39530-0006;6pos 5.08mm Pluggable
10;;;;GOLD CONTACT, FEMALE, 30-24AWG, CRIMP ;Molex;16-02-0097 ;gold crimp on reel
1;;;;ATO fuse 15A;Littelfuse;0287015.PXCN;15A ATO fuse
6;;;;WIRE-BOARD CONNECTOR RECEPTACLE, 4POS, 2.54MM ;Molex;50-57-9404 ;4P POSITIVE LATCH
3;;;;WIRE-BOARD CONNECTOR RECEPTACLE, 3POS, 2.54MM ;Molex;50-57-9403 ;3P POSITIVE LATCH
3;;;;WIRE-BOARD CONNECTOR RECEPTACLE, 2POS, 2.54MM ;Molex;50-57-9402 ;2P POSITIVE LATCH
6;;;;TERMINAL FEMALE DISCONNECT 3.18MM VIOLET;TE;7-520366-2;ULTRA-FAST RECEPT
3;;;;microswitches;Omron;SS-3GL13PT;microswitches
1;;;;USB A-B cable;;;USB A-B cable

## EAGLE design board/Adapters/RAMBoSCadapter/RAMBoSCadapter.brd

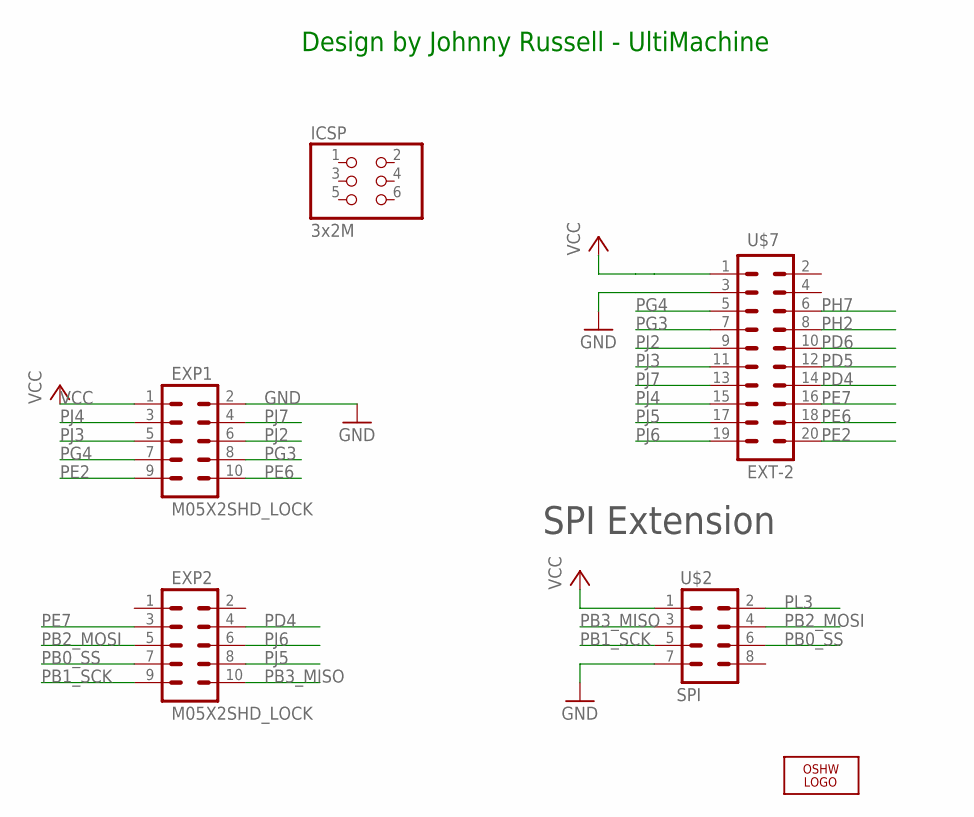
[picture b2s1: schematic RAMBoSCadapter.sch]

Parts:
EXP1, EXP2: M05X2SHD_LOCK; 2X5-SHROUDED_LOCK
ICSP: 3x2M; 2X03
LOGO1: OSHW_LOGO_8MILX0150-NT; OSHW_8X150_NOTEXT
U$2: SPI; 2X4
U$7: EXT-2; 2X10

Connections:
GND: EXP1.2, U$2.7, U$7.3
PB0_SS: EXP2.7, U$2.6
PB1_SCK: EXP2.9, U$2.5
PB2_MOSI: EXP2.5, U$2.4
PB3_MISO: EXP2.10, U$2.3
PD4: EXP2.4, U$7.14
PD5: U$7.12
PD6: U$7.10
PE2: EXP1.9, U$7.20
PE6: EXP1.10, U$7.18
PE7: EXP2.3, U$7.16
PG3: EXP1.8, U$7.7
PG4: EXP1.7, U$7.5
PH2: U$7.8
PH7: U$7.6
PJ2: EXP1.6, U$7.9
PJ3: EXP1.5, U$7.11
PJ4: EXP1.3, U$7.15
PJ5: EXP2.8, U$7.17
PJ6: EXP2.6, U$7.19
PJ7: EXP1.4, U$7.13
PL3: U$2.2
VCC: EXP1.1, U$2.1, U$7.1

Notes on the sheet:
SPI Extension
Design by Johnny Russell - UltiMachine

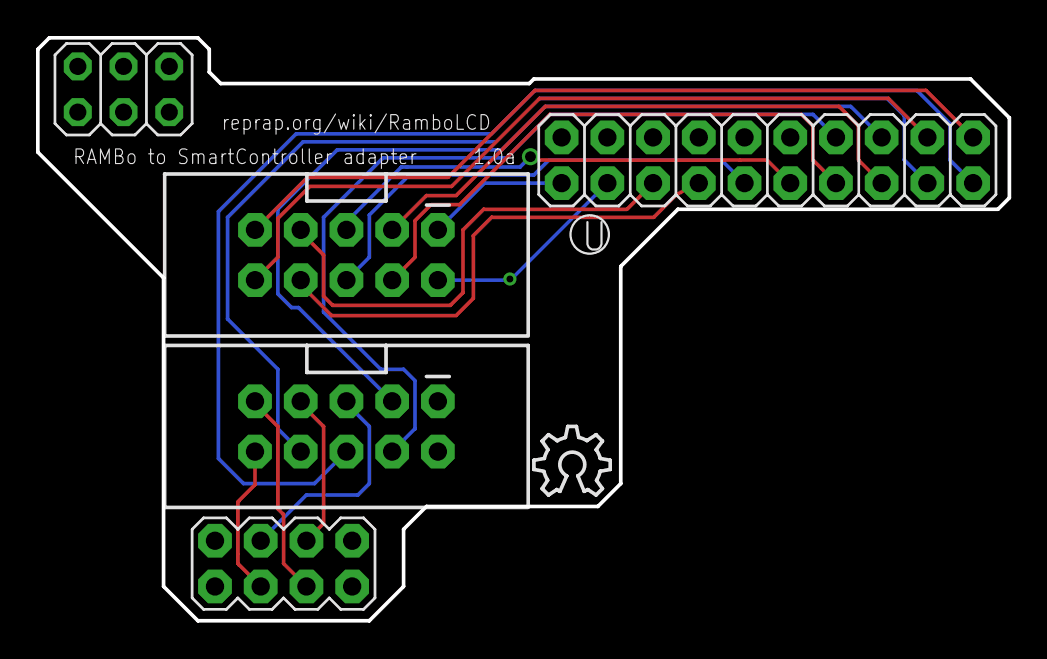
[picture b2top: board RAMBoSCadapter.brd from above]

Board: 2 copper layers, 54.0 x 32.4 mm, 6 parts (0 on the bottom side), 18 nets.

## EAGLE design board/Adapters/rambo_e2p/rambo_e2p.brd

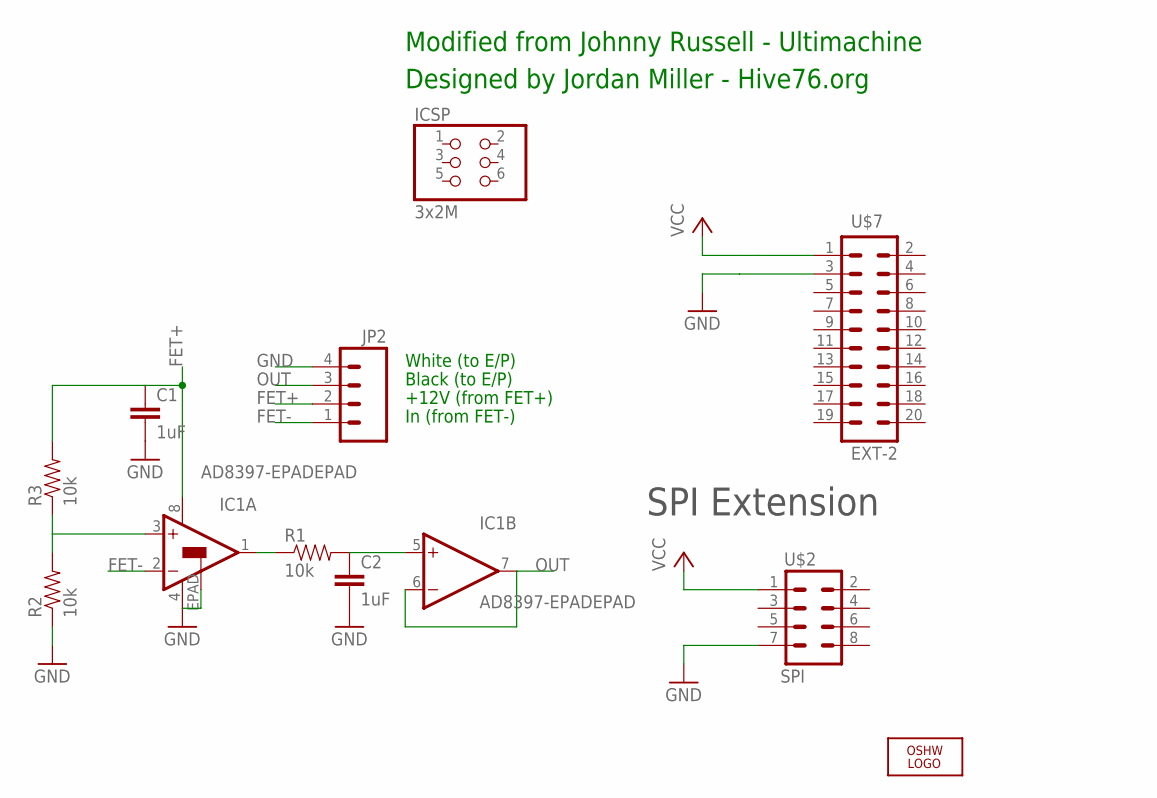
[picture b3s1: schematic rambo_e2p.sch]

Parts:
C1, C2: 1uF; 0805
IC1: AD8397-EPADEPAD; SO08-EPAD
ICSP: 3x2M; 2X03
JP2: M04SCREW; SCREWTERMINAL-3.5MM-4
LOGO1: OSHW_LOGO_8MILX0150-NT; OSHW_8X150_NOTEXT
R1, R2, R3: 10k; 0805
U$2: SPI; 2X4
U$7: EXT-2; 2X10

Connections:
FET+: C1.1, IC1.8 (V+), JP2.2, R3.2
FET-: IC1.2 (-IN), JP2.1
GND: C1.2, C2.2, IC1.4 (V-), IC1.EPAD, JP2.4, R2.1, U$2.7, U$7.3
unnamed: IC1.1 (OUT), R1.1
unnamed: C2.1, IC1.5 (+IN), R1.2
unnamed: IC1.3 (+IN), R2.2, R3.1
OUT: IC1.6 (-IN), IC1.7 (OUT), JP2.3
VCC: U$2.1, U$7.1

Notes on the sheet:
SPI Extension
+12V (from FET+)
White (to E/P)
Black (to E/P)
In (from FET-)
Modified from Johnny Russell - Ultimachine
Designed by Jordan Miller - Hive76.org

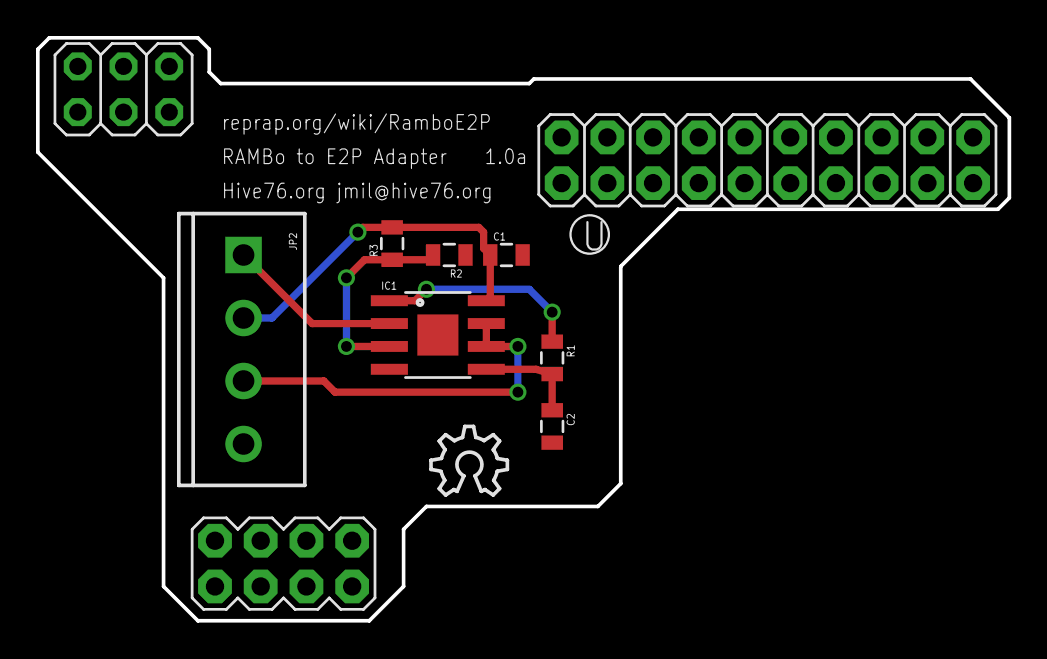
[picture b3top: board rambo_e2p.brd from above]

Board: 2 copper layers, 54.0 x 32.4 mm, 11 parts (0 on the bottom side), 8 nets.

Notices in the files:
board/History/RAMBo.sch:
Copyright 2013 - UltiMachine -Johnny,Britt,Dorothy,Lee,Bruce
parts and their libraries:
SparkFun: Licensing: CC v3.0 Share-Alike You are welcome to use this library for commercial purposes.
